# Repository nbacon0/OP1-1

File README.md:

The OP1:1 project is our effort to address an urgent need in the digital preservation community, namely that optical media (CDs, DVDS, etc.) are almost 40 years old, and are failing at an alarming rate: they're delaminating, suffering from disc rot and a slew of other issues.

Our proposed solution is a (completely open source) device to directly sample the laser as its reading the disc and storing this (very large) raw dump for safe-keeping and process later. The benefit of this approach is that it can be agnostic to the encoding of the discs. The same device that can preserve audio discs could be used to preserve video discs, photo discs, and other proprietary formats.
    
# Current Status
This project is currently months away from an initial release: parts have been ordered by the small group of volunteers and current resources regarding control of the OPU are being slowly assembled from parties that have engaged in research not directly addressing our need, but are still directly applicable to the goals outlined above.

###### Disclaimer
None of the below projects or resources are associated with the OP1:1 Project unless direclty noted.

# Resources

### Links to Projects that Contain Applicable Research and Resources

###### Project #1: Describes & provides a circuit to communicate with three diff. Blu-Ray OPUs

https://www.ncbi.nlm.nih.gov/pmc/articles/PMC6066758/

https://pubs.acs.org/doi/suppl/10.1021/acssensors.8b00340/suppl_file/se8b00340_si_001.pdf

###### Project #2: Reverse engineering the Xbox 360 OPU

http://www.diyouware.com/node/161

https://www.digchip.com/datasheets/parts/datasheet/287/MLX75012.php (photodiode datasheet)

###### Project #3: Controlling blu-ray diode to etch material

https://wiki.das-labor.org/w/LaserExposer

https://github.com/das-labor/laser-exposer

###### Project #4 Bypassing DVD Drive Circuits to Read Raw Data

https://debugmo.de/2007/07/read-your-dvds-the-raw-way/

### Files, Programs & Tools

###### Project 1: Tools & Tool websites used / referenced in OPU Biosensing Paper

https://www.cdspeed2000.com/download.html - Opti Drive Control

http://qpxtool.sourceforge.net/download.html - QPxTools

http://www.k-probe.com/download-kprobe-k-probe.php - K-Probe

###### Project #4 Tools Developed (software library to deal with raw DVD (NRZI) bitstreams.)

https://github.com/tmbinc/libdvd

### Technical Resources

###### Playstation 3 & 4 Blu-Ray Drive Technical Notes

https://www.psdevwiki.com/ps4/Bluray_Drive

https://www.psdevwiki.com/ps3/Bluray_Drive

### Parts List

#### Development Gear
###### Preferred Dev Kit

$57.79 - https://tinyurl.com/y2vp9gc6 - Board (for additional I/O) 

$30.79 - https://tinyurl.com/y5bf4q26 - MCU (WaveShare STM32 Core Board + STM32F7 (8MB of RAM)

###### Breakout Boards

$7.19 - https://tinyurl.com/y5zseyle - Pack of 5 - FPC/FFC Flat Flexible Cable Adapter Board Connectors

$5.69 - https://tinyurl.com/y3howaey - Pack of 5 - FPC/FFC Flat Flexible Cable Adapter Board Connectors 

#### Drives
###### PS3 Drive + OPU

$25.89 - https://tinyurl.com/yxz4hrx3 - PS3 Drive (KEM-410CCA) International Shipping - Drive Option #1

$26.63 - https://tinyurl.com/y2wpv3ua - PS3 Drive (KEM-410CCA) International Shipping - Drive Option #2

$15.90 - https://tinyurl.com/y3cqtx5q - OPU + Sled (KEM-410CCA) International Shipping

$13.50 - https://tinyurl.com/y3bo29z2 - OPU Only (KEM-410CCA) International Shipping

###### Xbox 360 Drive & OPU
$15.50 - $50 (eBay France) - https://tinyurl.com/y4n3xux9 - Xbox 360 HD DVD Drive (international shipping)

 $5.69 - https://tinyurl.com/y4dnyeug - OPU + Sled (PHR-803T) International Shipping

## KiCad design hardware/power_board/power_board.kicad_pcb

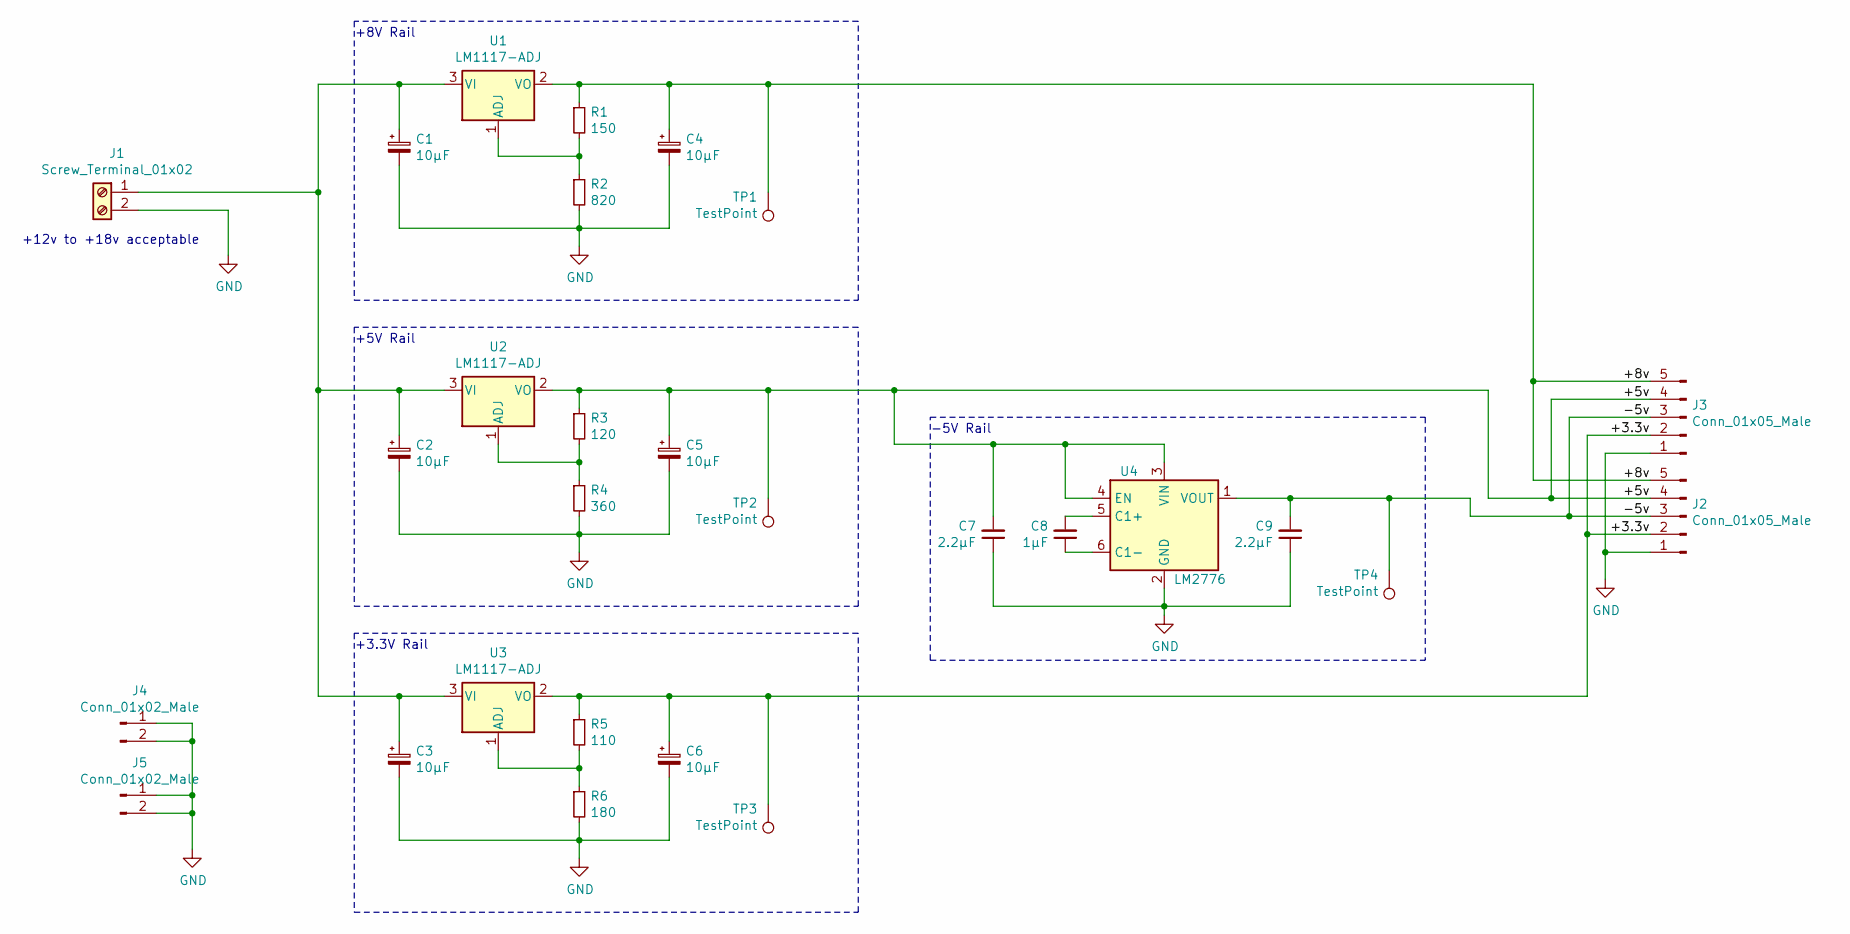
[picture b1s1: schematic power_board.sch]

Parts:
C1, C2, C3, C4, C5, C6: 10µF; C_1206_3216Metric; LCSC C7171
C7, C9: 2.2µF; C_0603_1608Metric; LCSC C23630
C8: 1µF; C_0603_1608Metric; LCSC C15849
J1: Screw_Terminal_01x02; TerminalBlock_Phoenix_PT-1,5-2-5.0-H_1x02_P5.00mm_Horizontal
J2, J3: Conn_01x05_Male; PinHeader_1x05_P2.54mm_Vertical
J4, J5: Conn_01x02_Male; PinHeader_1x02_P2.54mm_Vertical
R1: 150; R_0603_1608Metric; LCSC C22808
R2: 820; R_0603_1608Metric; LCSC C23253
R3: 120; R_0603_1608Metric; LCSC C22787
R4: 360; R_0603_1608Metric; LCSC C25194
R5: 110; R_0603_1608Metric; LCSC C22781
R6: 180; R_0603_1608Metric; LCSC C22828
TP1, TP2, TP3, TP4: TestPoint; TestPoint_Pad_D1.5mm
U1, U2, U3: LM1117-ADJ; SOT-223-3_TabPin2; LCSC C7920
U4: LM2776; SOT-23-6; LCSC C69527

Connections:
/+3.3v: C6.1, J2.2, J3.2, R5.1, TP3.1, U3.2 (VO)
/+5v: C5.1, C7.2, J2.4, J3.4, R3.1, TP2.1, U2.2 (VO), U4.3 (VIN), U4.4 (EN)
/+8v: C4.1, J2.5, J3.5, R1.1, TP1.1, U1.2 (VO)
/-5v: C9.2, J2.3, J3.3, TP4.1, U4.1 (VOUT)
GND: C1.2, C2.2, C3.2, C4.2, C5.2, C6.2, C7.1, C9.1, J1.2, J2.1, J3.1, J4.1, J4.2, J5.1, J5.2, R2.2, R4.2, R6.2, U4.2 (GND)
unnamed: C1.1, C2.1, C3.1, J1.1, U1.3 (VI), U2.3 (VI), U3.3 (VI)
unnamed: C8.1, U4.6 (C1-)
unnamed: C8.2, U4.5 (C1+)
unnamed: R1.2, R2.1, U1.1 (ADJ)
unnamed: R3.2, R4.1, U2.1 (ADJ)
unnamed: R5.2, R6.1, U3.1 (ADJ)

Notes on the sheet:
+5V Rail
+3.3V Rail
+8V Rail
-5V Rail
+12v to +18v acceptable

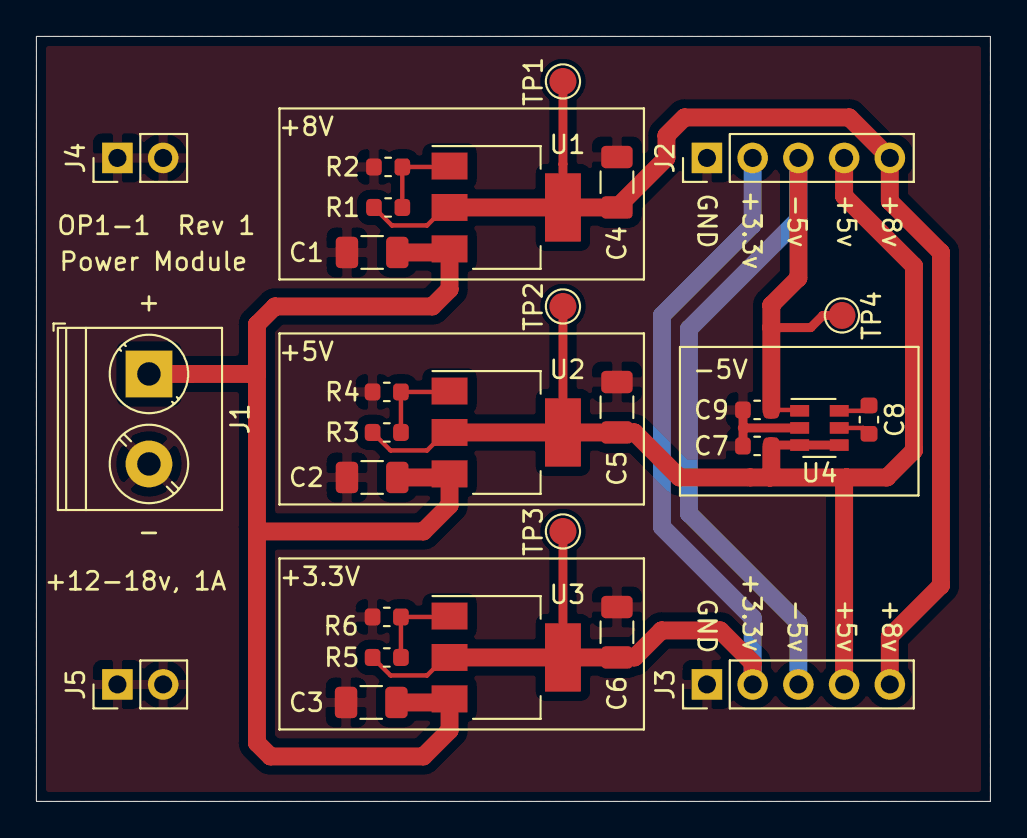
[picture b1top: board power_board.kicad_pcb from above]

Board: 2 copper layers, 53.0 x 42.5 mm, 28 parts (0 on the bottom side), 11 nets.

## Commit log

2019-11-13 Initial commit of the dev platform
2020-01-09 Added technical work document
2020-01-09 Added the biosensing schematic, with some annotations
2020-01-11 Added power board module
2020-01-11 Made the board design a little more spacious
